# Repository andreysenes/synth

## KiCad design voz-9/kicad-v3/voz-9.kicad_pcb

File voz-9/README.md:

# VOZ-9

Synth de mesa semi-modular em 9 V. Dois osciladores batendo, waveshaper de germânio, filtro, VCA com decay e fita de **três heads** (3× PT2399: flutter + saturação + repeats escuros). Família Look Mum No Computer / Noise Toaster / Ciat-Lonbarde.

A cadeia interna já toca sozinha. Os jacks só quebram ou desviam o fluxo.

```
 MIC ── XLR IN ── 5532 ── PRE ──┬── SEND (pré-EQ) ── RCV / fita
                                └── OSC IN (CW) ──┐
 OSC A/B/noise ──────────────────── OSC IN (CCW) ─┴── mix
                                                      │
                                                 EQ 424 → SHAPE → VCF → VCA
                                                      │
                                                 NAB → FITA → WET → VOLUME → OUT
```

Sem XLR, **PRE** escala os oscs. **OSC IN** = mix osc ↔ mic (CCW = só drones, CW = só voz).

O pré vocal está em `pre-vocal.md`. Mesmo papel do Echo Master, **sem transformador** (diferencial no NE5532 + pad no XLR).

Leia `esquema.md` para montar. Caderno de estudo: `componentes.md`. A referência
artesanal THT/fenolite está em `pcb.md`; o baseline KiCad atual é FR-4 de duas
camadas com PCBA SMD JLCPCB e montagem manual do restante. Para trabalhar no
KiCad via MCP, comece por `kicad-requisitos.md` e depois siga
`kicad-layout-agent.md`. O projeto KiCad (somente esquema, folhas picadas)
está em `kicad/voz-9.kicad_pro` — **sem PCB** até validação. Lista de compra:
`bom.md`. Simulador: `sim/painel.html`.

O baseline KiCad acrescenta um **VU analógico compacto de saída**: frontal
nominal 37 × 35 × 35 mm, 21 g, movimento 500 µA/630 Ω e iluminação quente por
filamento 6–12 V, sempre ligada com o equipamento. O chicote J10 separa
movimento e lâmpada. **0 VU = 0 dBV = 1,000 Vrms** pós-VOLUME/pré-pads.
Balística alvo de VU clássico: aproximadamente 300 ms, sem peak-hold. Recorte,
dimensões, consumo e resposta reais serão confirmados numa amostra antes de
atualizar `painel.svg`. O LED CLIP acende 1 dB antes do clipping real medido e
retém a indicação por aproximadamente 150 ms.

Também acrescenta nove indicadores em J11: **CLIP, GATE/ENV, LFO, OSC A/B,
H1–H3 e STACK**. Com o POWER existente, são **10 LEDs vermelhos difusos de
3 mm e baixo consumo**, com alvo de **1,5 mA por LED**. Lógica e polos das
chaves serão definidos antes do painel/BOM finais; CLIP, GATE/ENV e LFO usam
drivers discretos SMD, sem firmware. O brilho de GATE/ENV acompanha ataque e
decay do envelope; LFO pisca de forma binária e apaga com TREM no centro/OFF.

---

## Painel

**Um módulo só**, caixa de mesa. A referência legada usa faceplate **220 × 160 mm**; o baseline KiCad usa faceplate de alumínio **300 × 300 × ~2 mm** e caixa externa a ela (envelope provisório **336 × 336 mm**, paredes 15–18 mm, altura interna **60 mm**). A BASE mede **200 × 150 mm** e fica no fundo. **P4 e combos IN/OUT ficam no faceplate**, com o restante dos controles. O alumínio liga-se ao GND pelas **porcas** e por **fio isolado dedicado**. Headers **J1–J11 na borda inferior**, ordenados pela lógica do sinal. Legendas em **silkscreen direto no alumínio** (referência visual: `refs/faceplate-silk-reference.png`). A **posição fina** dos itens no faceplate fica para o acabamento. J1–J9 são a referência de pinagem legada; o baseline acrescenta **J10 para o VU analógico e J11 para indicadores**.

```
 IN  PRE  OSC IN | LED 9V          OSC A  AMOUNT  OSC B
 LOW  MID F  MID G  HIGH           A  B  SHAPE  CUTOFF  DRONE  GATE
 RATE  TREM  MODE  DEPTH
 TIME  WET  F-BACK  H1  H2  H3  STACK     |  VOLUME
 A B IN FILT FCV VCV LFO ECV CLK SEND RCV |  OUT
```

- **Esquerda:** entrada + EQ + LFO. XLR no canto superior esquerdo.
- **Direita:** osciladores + A/B/SHAPE/CUTOFF/DRONE/GATE.
- **Delay:** TIME · WET · F-BACK · H1 · H2 · H3 · STACK.
- **VOLUME** e **OUT** na célula direita.

Knobs: OSC A/B, TIME, F-BACK, VOLUME = **Ø30 mm**; o resto **Ø15 mm**. VOLUME = chicken-head vermelho.

### Knobs

| Knob | Pot | Função |
| --- | --- | --- |
| **PRE** | A100 k | Nível do mic → SEND (pré-EQ); sem XLR = pré dos oscs |
| **OSC IN** | A100 k | Mix osc (CCW) ↔ XLR (CW) |
| **LOW / MID F / MID G / HIGH** | 4× 100 kB | EQ voz estilo 424 (pós-mix) |
| **OSC A / OSC B** | 500 kA | Pitch grave / agudo |
| **AMOUNT** | 100 kA | Balanço A ↔ B |
| **SHAPE** | 1 kB | Drive no germânio |
| **CUTOFF** | 100 kA | Corte do filtro |
| **RATE** | 100 kC | Velocidade do LFO |
| **DEPTH** | 25 kB | Quanto o LFO mexe no destino |
| **TIME** | 10 kB | Tempo das três heads |
| **WET** | A100 k | Seco ↔ molhado do eco |
| **F-BACK** | B100 k | Feedback / repeats |
| **VOLUME** | 2 kB | Nível de saída |

Trimpots na BASE: teto do F-BACK (RV1) e ressonância do VCF (RV2).

### Chaves

| Controle | Tipo | Posições | Função |
| --- | --- | --- | --- |
| **OSC A / OSC B** | 2× SPST ON–OFF (MTS-101) | off / on | Liga cada oscilador |
| **H1 / H2 / H3** | 3× SPDT ON–ON (MTS-102) | off / on | Liga cada head. As três off = delay off |
| **TREM** | SPDT ON–OFF–ON (MTS-103) | tremolo / **off** / flutter | Faixa do LFO (centro = sem efeito) |
| **MODE** | SPDT ON–OFF–ON (MTS-103) | pitch / nada / time | Destino do DEPTH |
| **DRONE / GATE** | SPDT ON–ON (MTS-102) | drone / gate | Drone = VCA aberto. Gate = envelope |
| **STACK** | SPDT ON–ON (MTS-102) | off / on | Heads em série (com H1 on) |

Botão momentâneo **GATE**: dispara o envelope com a chave em **gate**. Em DRONE, mute momentâneo dos oscs A/B.

---

## Conectores de palco — combo XLR+P10

Dois **combo XLR+P10 clone** (não Neutrik): XLR fêmea e P10 no mesmo furo.

| Combo | Lado XLR | Lado P10 |
| --- | --- | --- |
| **IN** | SM58 → pré diferencial (5532) → PRE | guitarra → AMOUNT (mix dos oscs) |
| **OUT** | mesa, **nível de mic** (pad) | amp / interface, **nível de pedal** |

SEND / RCV do loop são dois P2 da fileira de patch (`bom.md`). Detalhe do pré: `pre-vocal.md`.

## Jacks de patch

Cadeia normalizada: se nada está plugado, o sinal corre sozinho. Jack com * quebra a cadeia.

| Jack | Tipo | O que faz |
| --- | --- | --- |
| A | P2 out | Oscilador A cru |
| B | P2 out | Oscilador B cru |
| IN | P2 in | Áudio extra no AMOUNT. Paralelo ao P10 do combo IN |
| FILT* | P2 in chaveado | Entrada do filtro. Sem cabo = vem do SHAPE |
| FCV | P2 in CV | Soma no cutoff (0–9 V) |
| VCV | P2 in CV | Soma no VCA / gate |
| LFO | P2 out | Saída do LFO |
| ECV | P2 in CV | Flutter/CV nos três heads |
| **CLK** | P2 in clock | Pulso 0–9 V. Puxa o TIME. **Não é MIDI** |
| SEND / RCV | loop | Antes da fita, 100 % (SEND = PRE, pré-EQ) |

Pinos P2: ponta = sinal, anel/sleeve = GND. CV é 0–9 V, sem 1 V/oitava. CLK: `esquema.md` §8.

---

## Como toca

1. DRONE on, VOLUME no meio, WET no meio, F-BACK baixo, SHAPE e DEPTH no mínimo, TIME no mínimo, AMOUNT no meio, **OSC IN** no CCW (só oscs) ou meio (blend).
2. Aproxima OSC A e OSC B até aparecer o batimento.
3. Abre CUTOFF e SHAPE. EQ flat = knobs no meio.
4. **TREM** em tremolo + MODE em pitch = vibrato. Em time = fita tremendo.
5. **TREM no meio** = LFO off (DEPTH não modula).
6. DRONE off, aperta GATE: nota com cauda. Com XLR, a fala também abre o ENV.
7. H1/H2/H3: as três off = delay off. Só H1 = slapback. As três on = Space Echo. STACK = série.
8. Mic no XLR: PRE a meio, OSC IN a meio = voz + drones. CW = só voz; CCW = só oscs.

### Patches

- **Guitarra no filtro** — P10 IN ou P2 IN → FILT.
- **LFO no filtro** — LFO → FCV, MODE no centro, TREM ≠ off.
- **Fita 3 heads** — H1+H2+H3, TREM em flutter, MODE em time, F-BACK às 3h.
- **Tremolo de volume** — TREM em tremolo, MODE no centro, LFO → VCV.
- **Slapback** — só H1, TIME no mínimo, F-BACK baixo.
- **Clock externo** — sync → CLK. MIDI → conversor → CLK.
- **Voz + drones** — SM58, PRE meio, OSC IN meio, EQ a gosto, GATE ou DRONE.

---

## O que comprar

Tudo novo: `bom.md`. Um instrumento ~R$ **610** (varejo BR, set/2026, sem frete).

J201: marque Vgs(off) nos 8. O mais “vivo” vai no VCF; um par parecido nos FM. MP20 por último — ferro baixo.

---

## Ordem de teste na protoboard

1. Fonte: 9 V, −9 V (MAX1044), 5 V (78M05), 4V5, 1V8. LED acende.
2. OSC A / OSC B / batimento.
3. SHAPE, CUTOFF, GATE / DRONE.
4. LFO + TREM (tremolo / off / flutter) + MODE.
5. 5532 + PRE + OSC IN (mix) + EQ 424 (U9).
6. TL072 NAB: VCA → GRAVA → H1 → LÊ.
7. PT2399 H1, H2, H3. Jacks e normals por último.

Detalhe: `esquema.md`. Placa: `pcb.md`.

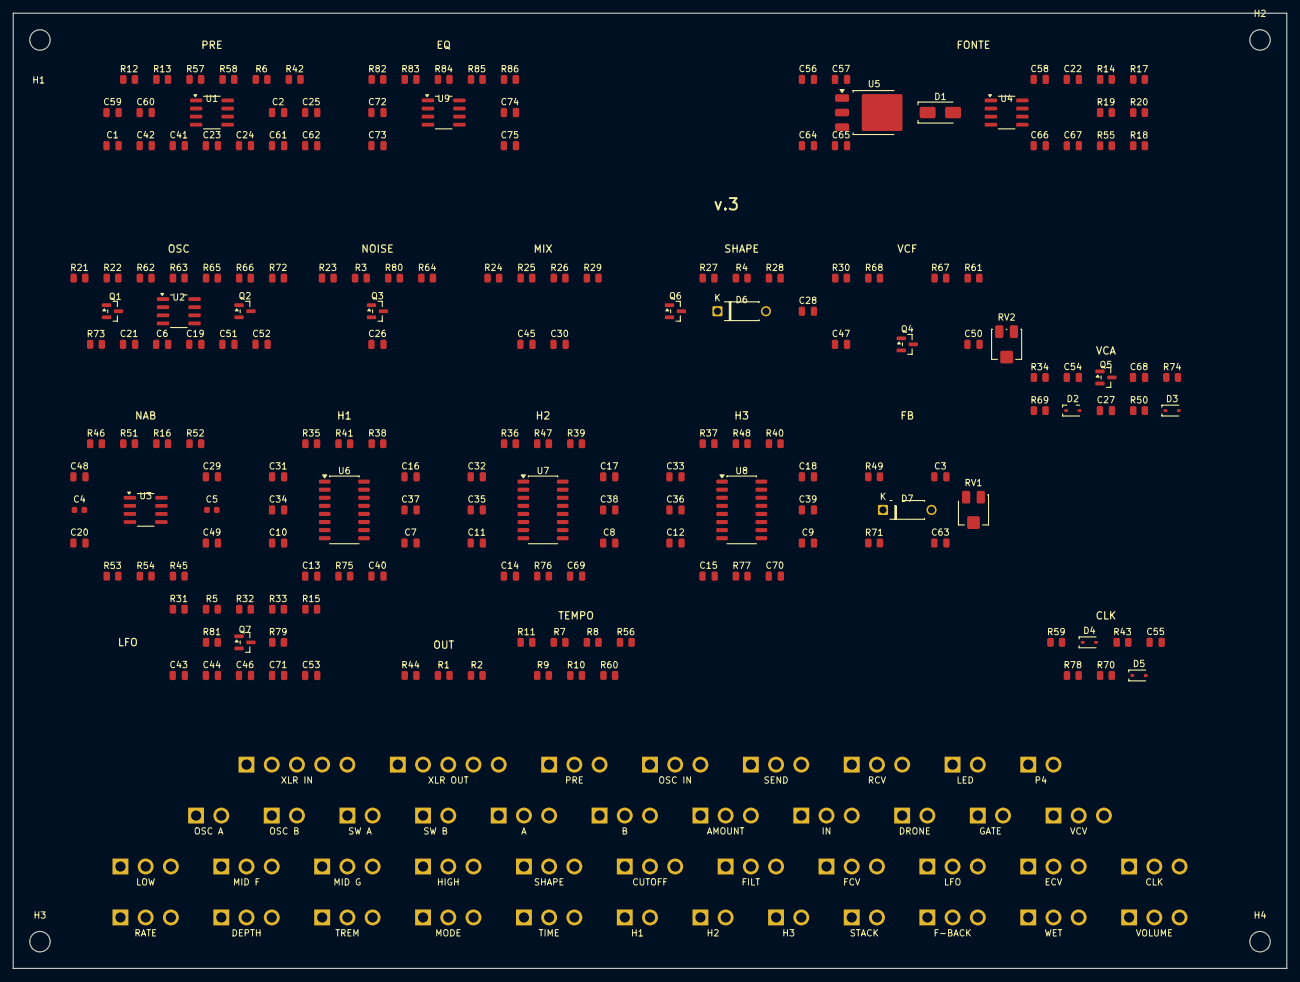
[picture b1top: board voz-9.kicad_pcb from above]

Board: 2 copper layers, 200.0 x 150.0 mm, 232 parts (0 on the bottom side), 144 nets, no tracks yet.

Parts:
C1, C2: 100p; C_0805_2012Metric
C3: 2n2; C_0805_2012Metric
C4, C5: 3n3; C_0603_1608Metric
C6, C7, C8, C9, C10, C11, C12, C13, C14, C15, C16, C17, C75: 10n; C_0805_2012Metric
C18: 22n; C_0805_2012Metric
C19, C20, C21, C22, C23, C24, C25, C26, C27, C28, C29, C30, C31, C32, C33, C34, C35, C36, C37, C38, C39, C40, C41, C42, C72: 100n; C_0805_2012Metric
C43, C44, C45, C46, C47, C48, C49, C50: 220n; C_0805_2012Metric
C51, C52: 1µ; C_0805_2012Metric
C53, C54: 2µ2; C_0805_2012Metric
C55: 4µ7; C_0805_2012Metric
C56, C57, C58, C59, C60, C61, C62, C63: 10µ; C_0805_2012Metric
C64, C65, C66, C67, C68, C69, C70, C71: 22µ; C_0805_2012Metric
C73: 33n; C_0805_2012Metric
C74: 1n; C_0805_2012Metric
D1: SS14; D_SMA
D2, D3, D4, D5: 1N4148WS; D_SOD-323
D6, D7: MP20; D_DO-41_SOD81_P7.62mm_Horizontal
H1, H2, H3, H4: M3; MountingHole_3.2mm_M3
J1: CUTOFF
J1#2: OSC A
J1#3: SHAPE
J1#4: SW B
J1#5: DRONE
J1#6: AMOUNT
J1#7: SW A
J1#8: OSC B
J2: MODE
J2#2: RATE
J2#3: DEPTH
J2#4: TREM
J3: H1
J3#2: WET
J3#3: H2
J3#4: STACK
J3#5: H3
J3#6: TIME
J3#7: F-BACK
J3#8: VOLUME
J4: VCV
J4#2: A
J4#3: IN
J4#4: FILT
J4#5: FCV
J4#6: B
J5: CLK
J5#2: RCV
J5#3: LFO
J5#4: SEND
J5#5: ECV
J6: LED
J6#2: GATE
J6#3: P4
J7: XLR IN
J7#2: PRE
J7#3: OSC IN
J8: XLR OUT
J9: MID G
J9#2: LOW
J9#3: HIGH
J9#4: MID F
Q1, Q2, Q3, Q4, Q5, Q6: MMBFJ201; SOT-23
Q7: MMBF5457; SOT-23
R1, R2: 220; R_0805_2012Metric
R3, R4, R5, R6, R7, R8, R9, R10: 1k; R_0805_2012Metric
R11: 2k; R_0805_2012Metric
R12, R13: 2k2; R_0805_2012Metric
R14, R15, R16, R17: 4k7; R_0805_2012Metric
R18: 5k6; R_0805_2012Metric
R19, R20, R21, R22, R23, R24, R25, R26, R27, R28, R29, R30, R31, R32, R33, R34, R35, R36, R37, R38, R39, R40, R41, R42, R43, R44, R45, R46, R47, R48, R49, R50, R71, R82, R83, R84: 10k; R_0805_2012Metric
R51, R52, R53, R54: 15k; R_0805_2012Metric
R55, R56, R57, R58: 22k; R_0805_2012Metric
R59: 47k; R_0805_2012Metric
R60, R61: 68k; R_0805_2012Metric
R62, R63, R64, R65, R66, R67, R68, R69, R70, R85: 100k; R_0805_2012Metric
R72, R73, R74, R75, R76, R77, R78, R79: 220k; R_0805_2012Metric
R80, R81: 1M; R_0805_2012Metric
R86: 3k3; R_0805_2012Metric
RV1, RV2: 100k; Potentiometer_Bourns_3314J_Vertical
U1: NE5532DR; SOIC-8_3.9x4.9mm_P1.27mm
U2, U3, U9: TL072CDR; SOIC-8_3.9x4.9mm_P1.27mm
U4: ICL7660; SOIC-8_3.9x4.9mm_P1.27mm
U5: 78M05; TO-252-3_TabPin2
U6, U7, U8: PT2399; SOP-16_4.4x10.4mm_P1.27mm

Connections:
AMT_W: J1#6.6, J7#3.9
CLK_A: D4.2, R43.1, R59.2
CLK_B: C55.1, D4.1, R70.1, R78.1
CLK_TIP: D5.2, J5.7, R59.1
CUT_W: J1.12, R68.1
DEPTH_W: J2.10, J2#3.5
DRY: C54.2, J3#2.13, R46.1
ENV: C68.1, D2.1, D3.1, J1#5.19, Q5.2, R69.1, R74.1
EQ_B: C72.1, J9.9, J9#2.3, J9#3.12, R83.1, U9.7
EQ_BUF: J9.7, J9#2.1, J9#3.10, R82.1, U9.1, U9.2
EQ_IN: C30.2, R85.1, U9.3
EQ_OUT: C72.2, J1#3.10, R27.1
EQ_SUM: C73.2, C74.2, R82.2, R83.2, R86.2, U9.6
EXT_IN: C45.2, J4#3.7, R26.1
FALA: C27.2, R50.1
FALA_A: D3.2, R50.2
FB_CW: J3#7.12, RV1.2, RV1.3
FCV: J4#5.13, R67.2
FILT_SW: C28.2, J4#4.11
FILT_TIP: J4#4.10, R30.1, RV2.1, RV2.3
GATE: D2.2, J6#2.6
GND: C1.2, C2.2, C3.2, C10.2, C11.2, C12.2, C16.2, C17.2, C18.2, C19.2, C22.2, C23.2, C24.2, C31.2, C32.2, C33.2, C37.2, C38.2, C39.2, C40.2, C47.2, C55.2, C57.2, C58.2, C61.2, C62.2, C63.2, C64.2, C65.2, C66.2, C67.2, C68.2, D6.1, D7.1, J1.13, J1#3.8, J1#6.5, J2#2.3, J2#3.4, J3#6.3, J3#7.10, J3#8.18, J4.18, J4#2.3, J4#3.9, J4#4.12, J4#5.15, J4#6.6, J5.9, J5#2.15, J5#3.3, J5#4.12, J5#5.6, J6.2, J6#3.4, J7.3, J7.5, J7#2.6, J8.3, J8.5, R1.2, R2.2, R3.2, R5.2, R6.2, R18.2, R20.2, R32.2, R33.2, R43.2, R58.2, R74.2, R78.2, R80.2, R81.2, R85.2, U2.4, U3.3, U3.5, U4.3, U5.2, U6.3, U6.4, U7.3, U7.4, U8.3, U8.4, U9.5
GRAVA_IN: C48.1, R51.2
H1_ON: J3.5, R38.1
H2A: R7.2, R8.1
H2B: R8.2, R56.1
H2_ON: J3#3.7, R39.1
H3A: R9.2, R10.1
H3B: R10.2, R60.1
H3_ON: J3#5.9, R40.1
HEADS: C20.2, R35.1, R36.1, R37.1
HIGH_W: C74.1, J9#3.11
INST_TIP: C45.1, J7.4
J8_COLD: J8.2, R2.1
LED_A: J6.1, R14.2
LE_IN: C29.2, R53.1
LFO_AC: C53.2, R79.1
LFO_D: C43.1, C53.1, Q7.1, R31.2
LFO_G: C46.2, C71.2, Q7.2, R15.1, R81.1
LFO_N1: C43.2, C44.1, R32.1
LFO_N2: C44.2, J2#4.7, R33.1
LFO_OUT: J2#3.6, J5#3.1, R79.2
LFO_S: Q7.3, R5.1
LOW_W: C73.1, J9#2.2
MIDF_CW: J9#4.6, R86.1
MIDF_W: C75.2, J9#4.4, J9#4.5
MIDG_W: J9.8, R84.1
MID_C: C75.1, R84.2
MIX: C30.1, J7#3.10
N1V8: C67.1, J1.11, J1#5.18, J6#2.5, Q4.3, R18.1, R34.2, R55.2
N4V5: C6.2, C21.2, C66.1, Q1.3, Q2.3, R4.2, R19.2, R20.1, R63.2, R73.2
NAB_BASS: C49.1, R45.2
NAB_MID: C48.2, R16.1
NOISE_D: C26.1, Q3.1, R23.2
NOISE_MIX: C26.2, R64.1
NOISE_S: Q3.3, R3.1
OSCIN_CW: C41.2, J7#3.11
OSC_A_POT: J1#2.1, R21.2
OSC_B_POT: J1#8.3, R22.2
OUT: J3#8.19, J8.4, R44.1
P4_TIP: D1.2, J6#3.3
PITCH_CV: J2.11, R65.1, R66.1
PRE_CW: C42.2, J7#2.8
PRE_R12: C59.2, R12.1
PRE_R13: C60.2, R13.1
PRE_W: C27.1, C41.1, J5#2.14, J5#4.10, J7#2.7
PT6_U6: R11.2, R75.2, U6.6
PT6_U7: R56.2, R76.2, U7.6
PT6_U8: R60.2, R77.2, U8.6
PT_REF_U6: C37.1, U6.2
PT_REF_U7: C38.1, U7.2
PT_REF_U8: C39.1, U8.2
Q1G: Q1.2, R65.2
Q2G: Q2.2, R66.2
Q3G: Q3.2, R80.1
Q4G: Q4.2, R67.1, R68.2
Q6G: Q6.2, R27.2
Q6S: Q6.3, R4.1, R28.1
RATE_W: J2#2.1, J2#2.2, R15.2
RES_W: R61.2, RV2.2
SHAPE: C28.1, D6.2, R28.2, R29.2
SHAPE_W: J1#3.9, R29.1
STAR: J3#7.11, J5#2.13, R46.2, R51.1
SUM: J1#6.7, R24.2, R25.2, R26.2, R64.2
SW_A: C51.2, J1#7.14
SW_A_ON: J1#7.15, J4#2.1, R24.1
SW_B: C52.2, J1#4.16
SW_B_ON: J1#4.17, J4#6.4, R25.1
TIME_CV: J2.12, J5#5.4, R70.2, R75.1, R76.1, R77.1
TIME_W: J3#6.2, R7.1, R9.1, R11.1
TREM_A: C46.1, J2#4.8
TREM_B: C71.1, J2#4.9
U1_BM: R6.1, R42.1, U1.6
U1_BP: C25.2, U1.5
U1_INM: R13.2, R57.1, U1.2
U1_INP: R12.2, R58.1, U1.3
U1_OA: C25.1, R57.2, U1.1
U1_OB: C42.1, R42.2, U1.7
U2A_INM: C21.1, J1#2.2, Q1.1, U2.2
U2A_INP: R62.2, R63.1, U2.3
U2A_OUT: C51.1, R21.1, R62.1, U2.1
U2B_INM: C6.1, J1#8.4, Q2.1, U2.6
U2B_INP: R72.2, R73.1, U2.5
U2B_OUT: C52.1, R22.1, R72.1, U2.7
U3A_IN: C4.1, R16.2, R52.1, U3.2
U3A_OUT: C4.2, C20.1, R52.2, U3.1
U3B_IN: C5.1, R45.1, R53.2, R54.1, U3.6
U4_CAP+: C56.1, U4.2
U4_CAP-: C56.2, U4.4
U6_CC0: C7.2, U6.8
U6_CC1: C7.1, U6.7
U6_IN: R35.2, R41.1, U6.16
U6_LP1: C10.1, C16.1, R41.2, U6.15
U6_OP: C13.1, U6.9, U6.10, U6.11, U6.12, U6.13
U6_OUT: C13.2, C34.1, U6.14
U6_SW: C34.2, J3.4, J3#4.16
U7_CC0: C8.2, U7.8
U7_CC1: C8.1, U7.7
U7_IN: J3#4.17, R36.2, R47.1, U7.16
U7_LP1: C11.1, C17.1, R47.2, U7.15
U7_OP: C14.1, U7.9, U7.10, U7.11, U7.12, U7.13
U7_OUT: C14.2, C35.1, C69.1, U7.14
U7_SW: C35.2, C69.2, J3#3.6
U8_CC0: C9.2, U8.8
U8_CC1: C9.1, U8.7
U8_IN: R37.2, R48.1, U8.16
U8_LP1: C12.1, C18.1, R48.2, U8.15
U8_OP: C15.1, U8.9, U8.10, U8.11, U8.12, U8.13
U8_OUT: C15.2, C36.1, C70.1, U8.14
U8_SW: C36.2, C70.2, J3#5.8
V5: C22.1, C31.1, C32.1, C33.1, C58.1, C63.1, J3#6.1, U5.3, U6.1, U7.1, U8.1
V9: C19.1, C23.1, C40.1, C61.1, C64.1, D1.1, D5.1, Q6.1, R14.1, R19.1, R23.1, R31.1, R55.1, U1.8, U2.8, U3.8, U4.8, U5.1, U9.8
VCA_D: C50.2, Q5.1
VCA_S: C54.1, Q5.3, R34.1
VCF: C47.1, C50.1, Q4.1, R30.2, R61.1
VCV: J4.16, R69.2
VEE: C24.1, C57.1, C62.1, C65.1, U1.4, U3.4, U4.5, U9.4
WET: C5.2, C49.2, D7.2, J3#2.15, R49.1, R54.2, R71.1, RV1.1, U3.7
WET_LP: C3.1, R49.2
WET_MIX: C29.1, R38.2, R39.2, R40.2
WET_W: J3#2.14, J3#8.20, R71.2
XLR_COLD: C2.1, C60.1, J7.2
XLR_HOT: C1.1, C59.1, J7.1
XLR_OUT: J8.1, R1.1, R44.2

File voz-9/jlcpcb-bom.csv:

Comment,Designator,Footprint,LCSC Part #
NE5532DR dual op-amp,U1,SOIC-8,C7426
TL072CDR dual JFET op-amp,U2 U3 U9,SOIC-8,C67473
ICL7660CSA voltage inverter (MAX1044),U4,SOIC-8,C42421900
L78M05ABDT-TR 5V 500mA,U5,TO-252-2,C58069
PT2399-SN echo processor,U6 U7 U8,SOP-16,C126407
MMBFJ201 N-JFET,Q1 Q2 Q3 Q4 Q5 Q6,SOT-23,C891687
MMBF5457 N-JFET,Q7,SOT-23,C2830807
SS14 Schottky 40V 1A (1N5817),D1,SMA,C2480
1N4148WS switching diode,D2 D3 D4 D5,SOD-323,C2128
220R 1% 0805,R1 R2,0805,C17557
1k 1% 0805,R3 R4 R5 R6 R7 R8 R9 R10,0805,C17513
2k 1% 0805,R11,0805,C17604
2.2k 1% 0805,R12 R13,0805,C17520
4.7k 1% 0805,R14 R15 R16 R17,0805,C17673
5.6k 1% 0805,R18,0805,C4382
10k 1% 0805,R19 R20 R21 R22 R23 R24 R25 R26 R27 R28 R29 R30 R31 R32 R33 R34 R35 R36 R37 R38 R39 R40 R41 R42 R43 R44 R45 R46 R47 R48 R49 R50 R71 R82 R83 R84,0805,C17414
15k 1% 0805,R51 R52 R53 R54,0805,C17475
22k 1% 0805,R55 R56 R57 R58,0805,C17560
47k 1% 0805,R59,0805,C17713
68k 1% 0805,R60 R61,0805,C17801
100k 1% 0805,R62 R63 R64 R65 R66 R67 R68 R69 R70 R85,0805,C149504
220k 1% 0805,R72 R73 R74 R75 R76 R77 R78 R79,0805,C17556
1M 1% 0805,R80 R81,0805,C17514
3.3k 1% 0805,R86,0805,C26010
100pF 50V C0G 0805,C1 C2,0805,C1790
1nF 50V X7R 0805,C74,0805,C46653
33nF 50V X7R 0805,C73,0805,C1739
2.2nF 50V C0G 0805,C3,0805,C28260
3.3nF 50V X7R 0603,C4 C5,0603,C1613
10nF 50V X7R 0805,C6 C7 C8 C9 C10 C11 C12 C13 C14 C15 C16 C17 C75,0805,C1710
22nF 50V X7R 0805,C18,0805,C1729
100nF 50V X7R 0805,C19 C20 C21 C22 C23 C24 C25 C26 C27 C28 C29 C30 C31 C32 C33 C34 C35 C36 C37 C38 C39 C40 C41 C42 C72,0805,C49678
220nF 50V X7R 0805,C43 C44 C45 C46 C47 C48 C49 C50,0805,C5378
1uF 50V X7R 0805,C51 C52,0805,C28323
2.2uF 50V X5R 0805,C53 C54,0805,C377773
4.7uF 25V X5R 0805,C55,0805,C1779
10uF 25V X5R 0805,C56 C57 C58 C59 C60 C61 C62 C63,0805,C15850
22uF 25V X5R 0805 (equiv 47u 16V),C64 C65 C66 C67 C68 C69 C70 C71,0805,C45783

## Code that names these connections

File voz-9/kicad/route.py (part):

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def build_nets():
    n = {}
    # --- fonte ---
    two(n, "D1", "V9", "P4_TIP")  # K = pino 1, A = pino 2
    add(n, "P4_TIP", ("J6", "3"))
    add(n, "GND", ("J6", "4"))
    two(n, "R14", "V9", "LED_A")
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    two(n, "R74", "ENV", "GND")
    two(n, "R69", "ENV", "VCV")
    add(n, "VCV", ("J4", "16"))
    # 1V8 ── botão NA ── 1N4148 ── ENV. O pino 6 é o ânodo, não o GND.
    add(n, "N1V8", ("J6", "5"))
    add(n, "GATE", ("J6", "6"), ("D2", "2"))
    add(n, "ENV", ("D2", "1"))
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        add(n, "PT_REF_" + ref, (ref, "2"))
        add(n, "GND", (ref, "3"), (ref, "4"))
        add(n, "PT6_" + ref, (ref, "6"))
        two(n, pin6_r, "TIME_CV", "PT6_" + ref)
        two(n, clk_c, ref + "_CC1", ref + "_CC0")
        add(n, ref + "_CC1", (ref, "7"))
        add(n, ref + "_CC0", (ref, "8"))
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def main():
    raw = build_nets()
    nets = collapse_aliases(raw)
    print(f"nets {len(nets)}  pins {sum(len(v) for v in nets.values())}")
    board = pcbnew.LoadBoard(BOARD)
    if "kicad-v2" in BOARD:
        import v2
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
